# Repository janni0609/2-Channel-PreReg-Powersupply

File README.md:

# 2-Channel Pre-Regulated Bench Power Supply

A two-channel laboratory bench power supply, **0–36 V / 0–2 A per channel**, fully
isolated between channels. Each channel pairs a **tracking switch-mode
pre-regulator** with a **linear post-regulator**, so it has the low output noise of
a linear supply without the heat of dropping 36 V across a pass transistor.

Everything here is open: KiCad 10 schematics and layout for both boards, the
firmware for all three microcontrollers, and the design calculations (loop
stability, DC/DC dimensioning, ADC/DAC error budget) that back the component
values.

**Status: built and working.** Both PCBs are assembled and running. One known
footprint error, see [Known issues](#known-issues).

**Schematics in your browser (KiCanvas):**
[Main board](https://kicanvas.org/?repo=https%3A%2F%2Fgithub.com%2Fjanni0609%2F2-Channel-PreReg-Powersupply%2Ftree%2Fmain%2Fhardware_main)
· [Front panel](https://kicanvas.org/?repo=https%3A%2F%2Fgithub.com%2Fjanni0609%2F2-Channel-PreReg-Powersupply%2Ftree%2Fmain%2Fhardware_front)

---

## Specifications

| Parameter | Value |
| --- | --- |
| Channels | 2, independent, galvanically isolated from each other and from the control logic |
| Output voltage | 0 … 36 V per channel |
| Output current | 0 … 2 A per channel (setpoint = current limit, CV/CC) |
| Setpoint resolution | 12-bit DAC ≈ 8.6 mV / 0.49 mA; front panel edits in 10 mV / 1 mA steps |
| Measurement resolution | 16-bit ADC, ~1.9 mV / ~0.1 mA; displayed as 3 decimals (V) and 4 decimals (A) |
| Accuracy | ±3–4 % uncalibrated (DAC band gap dominates). **Measured after calibration, worst of both channels: setpoint ±17 mV / ±1.3 mA, readback ±2.8 mV / ±3.7 mA** — see [Measured accuracy](#measured-accuracy) |
| Protection | Per-channel over-temperature (settable, default 60 °C), system OTP on the heatsink, comms-loss shutdown, input fuses + TVS |
| Regulation | Analog CV and CC loops per channel; MCU sets the references, does not close the loop. CC is indicated by a panel LED driven straight from the loop |
| Display | 256×64 SSD1322 OLED |
| Remote control | SCPI over Ethernet (raw TCP, port 5025) and USB CDC (front-panel USB-C) |
| Cooling | Temperature-controlled 4-wire PWM fan |
| Input | 2 × 40 V DC (channels) + 12 V DC (logic) — see [Power input](#power-input) |

---

## How it works

### Power path (one channel)

```text
40 V in ──▶ LT8612 tracking buck ──▶ Vpre = Vout + 2.2 V ──▶ TIP125 linear pass ──▶ OUT
                    ▲                                              ▲
                    └────────── follows the output ────────────────┘
```

The buck converter does not produce a fixed rail — it **tracks the output**,
holding just 2.2 V of headroom across the linear stage. At full load that is
~200 mV across the 0.1 Ω shunt plus ~2 V across the TIP125 Darlington, i.e. a few
watts of dissipation instead of the ~70 W a plain 40 V linear supply would burn at
0 V out into 2 A.

The linear stage is a classic op-amp regulator built around a **TIP125** PNP
Darlington driven by a **TLV4387** quad op-amp:

- **Voltage loop** — a 4-resistor difference amplifier across OUT+/OUT− scales the
  output by 1/15 (0.06935) and compares it against `Vset` from the DAC.
- **Current loop** — a 0.1 Ω shunt (PCS2512, 1 %, 0.4 W at 2 A) is amplified ×12.25
  and compared against `Iset`. Whichever loop demands less current wins, giving
  automatic CV → CC crossover. The crossover point itself is picked off as a
  `CC/CV` signal that lights the front-panel **CC** lamp directly — no firmware in
  the path, so the indicator is as fast as the loop it reports on.

Both loops are compensated deliberately, not guessed — see
[`Calc/Stability/`](Calc/Stability/) for the plant models, the chosen compensator
values, and the loop-gain / step-response plots.

Per-channel auxiliary rails come off the 40 V input: **LMR51606** buck → 4.5 V,
**AP7384-33Y** → 3.3 V for the MCU and converters, and an **LM2776** charge pump +
**XC6901** negative LDO → −1.2 V so the op-amps can swing cleanly down to 0 V.

### Control architecture

```text
        ┌──────────────── Front panel ────────────────┐
        │  SSD1322 OLED · encoder · 6 buttons · LEDs  │
        └──────────────────────┬──────────────────────┘
                               │ SPI / I²C
                    ┌──────────┴──────────┐        ┌──────────────┐
   Ethernet ────────┤   RP2350 "Brain"    ├────────┤ W5500 · USB  │ SCPI
                    └─────┬─────────┬─────┘        └──────────────┘
                UART0 ◄───┘         └───► UART1     (1 Mbps, ISO6721 isolated)
                  │                         │
        ┌─────────┴────────┐      ┌─────────┴────────┐
        │ ATtiny1614  CH1  │      │ ATtiny1614  CH2  │
        │ ADS1118 · MCP48F │      │ ADS1118 · MCP48F │
        └──────────────────┘      └──────────────────┘
```

Each channel has its own **ATtiny1614** living in that channel's isolated ground
domain. It drives the **MCP48FVB22** dual DAC (the V and I references for the
analog loops), reads the **ADS1118** 16-bit ADC (output voltage and shunt current),
monitors an NTC, sequences the two enable lines, and stores its calibration in
EEPROM. Over-temperature shutdown happens in the channel MCU itself, so a hung
UART link can never leave an output enabled.

The **RP2350** brain owns the user interface and all remote control. It never
touches the analog loops directly; it only sends setpoints and reads telemetry
over the two isolated 1 Mbps UART links.

---

## Boards

### `hardware_main/` — main board (`DualPreRegPowerSupply.kicad_pro`)

Both power channels, both channel MCUs, the brain, and the digital supply on one
PCB. Hierarchical sheets:

| Sheet | Contents |
| --- | --- |
| `Ch1Power` (×2 instances) | One complete channel — the sheet below is instantiated twice |
| ├ `Input` | 40 V input, fuse, TVS, common-mode choke |
| ├ `Power` | Channel aux rails: 4.5 V, 3.3 V, −1.2 V |
| ├ `DCDCTracking` | LT8612 tracking pre-regulator |
| ├ `Linear_PostReg` | TIP125 pass element, V and I loops, shunt, sense amps |
| ├ `DAC_ADC` | MCP48FVB22 DAC, ADS1118 ADC, filtering |
| └ `MCU` | ATtiny1614, NTC, ISO6721 isolated UART, UPDI header |
| `Control` | RP2350-Tiny, W5500 Ethernet, front-panel connectors, fan |
| └ `Digi_Power` | 12 V input → AP63200WU → 3.3 V logic rail |

Fabrication outputs (Gerbers, BOM, CPL) are in
[`hardware_main/production/`](hardware_main/production/); an interactive BOM is at
[`hardware_main/bom/ibom.html`](hardware_main/bom/ibom.html).

### `hardware_front/` — front panel (`Front Panel.kicad_pro`)

The user interface board: SSD1322 OLED header, rotary encoder with push button,
6 push buttons, 6 status LEDs (per channel: two green output-ON indicators, one
over each banana-jack pair, plus the red CC lamp), buzzer, and an **MCP23008** I²C
expander that collects the buttons and drives the buzzer. The green indicators run
off the corresponding channel's isolated 3.3 V rail, so each half of the panel
stays in its own ground domain. Fabrication outputs in
[`hardware_front/production/`](hardware_front/production/).

---

## Firmware

Both projects build with **PlatformIO**.

### `firmware/brain/main/` — RP2350 brain

Waveshare RP2350-Tiny (built against `waveshare_rp2350_zero`). Handles the OLED
UI, encoder and buttons, fan control, the UART links to both channels, and the
SCPI server on Ethernet + USB.

```sh
cd firmware/brain/main
pio run                 # build
pio run -t upload       # flash (UPF2 / USB bootloader)
```

RP2350 pin map (also documented at the top of `platformio.ini`):

| Function | Pins |
| --- | --- |
| OLED SSD1322 (SPI1) | RES 9, SCK 10, MOSI 11, DC 12, CS 13 |
| Rotary encoder (PIO quadrature) | A 14, B 15 |
| W5500 Ethernet (SPI0) | CS 17, SCK 18, MOSI 19, MISO 20, RST 21, INT 22 |
| MCP23008 expander (I²C1) | SDA 6, SCL 7, INT 8 |
| Channel UARTs @ 1 Mbps | CH1: TX 0 / RX 1 · CH2: TX 4 / RX 5 |
| Heatsink NTC / fan PWM | ADC3 (GPIO29) / GPIO26 (25 kHz) |

[`firmware/brain/UI-test/`](firmware/brain/UI-test/) is the earlier UI-only
prototype the production firmware grew out of; it is kept for display work without
the power hardware attached.

### `firmware/channel/` — ATtiny1614 channel

megaTinyCore, 16 MHz internal oscillator, flashed over UPDI. Layered cooperative
super-loop with an explicit state machine
(`INIT → SELFTEST → IDLE ↔ RUN → FAULT`). See
[`firmware/channel/README.md`](firmware/channel/README.md) for the module tree,
the state machine, and the calibration procedure.

```sh
cd firmware/channel
pio run -t fuses        # once: set OSCCFG to 16 MHz (required!)
pio run -t upload       # flash over UPDI
```

> The `-t fuses` step is not optional on a fresh part. The default fuse selects the
> 20 MHz oscillator base; with a 16 MHz build every timing (UART baud, delays,
> telemetry period) comes out 25 % off.

### Brain ↔ channel protocol

A small binary framing: `[SOF 0xA5][LEN][CMD][payload][CRC8]`, defined in
`firmware/channel/include/protocol.h` (mirrored into the brain project). The
channel pushes a telemetry frame every 100 ms (V, I, P, temperature, state,
flags) and ACK/NACKs every command. If the brain goes quiet for 1 s while an
output is on, the channel turns that output off by itself.

---

## Remote control (SCPI)

The instrument speaks an **SCPI-1999 / IEEE-488.2 subset** on two transports at
once — raw TCP port 5025 over Ethernet, and USB CDC — so it works with PyVISA,
NI-MAX, `lxi`, or a plain terminal.

```text
*IDN?                 → PreReg,PSU-2CH-36V2A,SN00001,0.2.0
APPL CH1,12.0,1.0
OUTP ON,(@1)
MEAS:VOLT? (@1)       → 12.001
MEAS:CURR? (@1)       → 0.2531
```

Channel lists (`(@1)`, `(@1,2)`) and stateful `INST:NSEL` selection are both
supported, along with the STATus register model, an error queue, and the
CALibration subsystem. The full command reference — including UART mappings and
known deviations — is in [`firmware/SCPI/commands.md`](firmware/SCPI/commands.md).

Network settings (DHCP or static IP, netmask, gateway, hostname) are configured
from the front panel under *Settings → Network*, and only take effect on **Apply**,
so a half-typed IP never goes live.

---

## Front panel

The main screen shows both channels side by side: measured voltage and current in
large digits, output power in the corner, and the active setpoints on the bottom
row. Six buttons (`V · on · I` per channel) select what the encoder edits and
toggle each output; the encoder push button moves the digit cursor — underlined on
screen — so any digit can be dialled directly instead of scrolling through the
whole range.

Below the buttons, each channel has two green output-ON LEDs flanking a red **CC**
lamp that lights whenever that channel leaves constant-voltage regulation, then the
output banana jacks. The USB-C port for SCPI-over-USB and firmware updates sits in
the middle of the panel; the mains switch is on the right. The enclosure is 3D
printed.

The Settings menu (encoder-driven, see
[`firmware/brain/UI-test/Settings.md`](firmware/brain/UI-test/Settings.md))
covers per-channel diagnostics (temperature, DAC/ADC/comms health, operating
hours, stored calibration values, the manual 2-point calibration wizard), the
temperature and fan curve (start temp, max temp, minimum speed, system OTP),
the network configuration, and system items (firmware version, beeper, brain
runtime, remember-setpoints-on-restart).

---

## Calibration

Every signal path — `VSET`, `ISET`, `VMEAS`, `IMEAS`, per channel — is a straight
line `y = gain·x + offset` fitted from two points and stored in the channel's
EEPROM. This is **required**, not optional: the MCP48FVB22 uses its internal
1.22 V band gap (Vref is not routed on the PCB), and that band gap is specified to
±3.3 %. Calibration removes it, along with the 1 % resistor and shunt tolerances,
leaving roughly ±0.05 % on voltage and ±0.1–0.2 % on current. Until a channel has
been calibrated it reports `FLAG_CAL_INVALID`.

Run it from the front panel (*Settings → Channel n → Manual Cal V/I*, with a
DMM on the output) or remotely via `CAL:POIN` / `CAL:COMM`. Full error budget and
where each term comes from:
[`Calc/DAC_ADC/DAC_ADC_Accuracy_Analysis.md`](Calc/DAC_ADC/DAC_ADC_Accuracy_Analysis.md).

---

## Measured accuracy

Both channels were measured against a **Siglent SDM3065X** 6½-digit DMM on
2026-08-03/04, using [`Calc/evaluation/psu_accuracy.py`](Calc/evaluation/) — a
ramp of the full range in fine steps, comparing three numbers at every step:

| | source | exercises |
| --- | --- | --- |
| setpoint | what was written with `VOLT` / `CURR` | DAC → `VSET`/`ISET` chain |
| readback | `MEAS:VOLT?` / `MEAS:CURR?` | sense amp → ADC → `VMEAS`/`IMEAS` chain |
| truth | SDM3065X | — |

Voltage: 0 → 36 V in 500 mV steps, open circuit. Current: 0 → 2 A in 25 mA steps
into the DMM's own current input as the load, 2 V compliance. Figures are for the
instrument **as it stands today**, i.e. calibrated, and exclude the two endpoints
the channel physically cannot reach: the 0 V / 0 A setpoint (output floor, not an
accuracy error) and the clipped top of the current range (see
[Known issues](#known-issues)). `psu_accuracy.py` applies both exclusions itself,
so these numbers come straight out of its report; `--keep-endpoints` reports every
point instead.

### Results

| | CH1 setpoint | CH1 readback | CH2 setpoint | CH2 readback |
| --- | --- | --- | --- | --- |
| **Voltage** rms | 8.8 mV | **0.74 mV** | 5.1 mV | 1.4 mV |
| worst | 16.5 mV | 2.1 mV | 11.6 mV | 2.8 mV |
| gain error | −0.0005 % | +0.0025 % | −0.0024 % | −0.0003 % |
| **Current** rms | **0.30 mA** | 0.12 mA | **0.52 mA** | 0.16 mA |
| worst | 0.79 mA | 0.39 mA | 1.36 mA | 0.51 mA |
| gain error | +0.012 % | +0.013 % | +0.035 % | +0.019 % |

Both current columns were re-measured on 2026-08-04, after the measure-path
calibration bug was found and fixed and both channels' `IMEAS` re-calibrated.
The readback paths went from 0.78 mA rms / +0.135 % gain / −1.38 mA offset (CH1)
and 2.0 mA rms / +0.176 % gain (CH2) to the numbers above — an order of
magnitude, and the −1.4 mA offset that had been blamed on the shunt turned out to
be an artefact of the bad fit.

In short, worst of both channels: **voltage setpoint ±17 mV (≈0.05 % FS), voltage
readback ±2.8 mV, current setpoint ±1.4 mA (≈0.07 % FS), current readback
±0.51 mA**. Every voltage gain error is inside ±0.003 % and every current gain
error is now inside ±0.04 %, so the calibration is doing its job on every path.
The current readback is at ~5 ADC LSB worst case.

<picture>
  <source media="(prefers-color-scheme: dark)" srcset="Calc/evaluation/results/ramp_v_ch1_20260804_231349_ch1_v_baseline_dark.png">
  
</picture>

The voltage setpoint trace is the interesting one. Its error is **not**
calibration error — it is the 12-bit DAC. The sawtooth is the ±½ LSB rounding of
a requested millivolt onto the ~8.9 mV code grid, and the slow envelope on top is
the DAC's own INL (specified ±2 LSB). A 2-point calibration pins the two
endpoints and cannot bend to follow a bow between them, which is why
re-calibrating an already-calibrated channel here changes nothing. The readback
trace sits flat at the ADC's ~1.8 mV quantum. **This is the hardware floor, not a
tuning problem** — improving it needs an external DAC reference (the `Vref` pin is
not routed) or more DAC bits.

<picture>
  <source media="(prefers-color-scheme: dark)" srcset="Calc/evaluation/results/ramp_i_ch1_20260804_224335_ch1_imeas_fix_dark.png">
  
</picture>

Current is the opposite case, and shows what calibration *can* do. Both of CH1's
current paths were a clean tilt beforehand — an error proportional to reading,
which is exactly the shape a 2-point fit removes. The setpoint went from +0.176 %
gain (−1.2 mA at 100 mA rising to +1.8 mA at 2 A) to +0.012 %, rms 0.89 →
0.30 mA; the readback went from +0.135 % gain with a −1.38 mA offset to
+0.013 %, rms 0.78 → 0.12 mA. Both traces are now flat inside ±0.8 mA across the
range, with the readback at ~4 ADC LSB. CH2 behaves the same way.

**Rule of thumb from this:** plot the error against reading before calibrating. A
*tilt*, or a constant offset, is gain/offset error and a 2-point fit removes it
exactly. A *bow* between the cal points is INL and it will not — which is why the
voltage setpoint above does not improve however often it is re-run. The report's
`worst non-linearity` row measures that bow; compare it against the quantisation
floor printed beneath it.

All raw data, per-run reports and both channels' plots are in
[`Calc/evaluation/results/`](Calc/evaluation/results/); the harness, wiring and
options are documented in [`Calc/evaluation/README.md`](Calc/evaluation/README.md).

---

## Power input

The supply is fed from three off-the-shelf Mean Well modules:

| Input | Supply | Feeds |
| --- | --- | --- |
| J101 | Mean Well **LRS-75-36**, trimmed to **40 V** | Channel 1 |
| J601 | Mean Well **LRS-75-36**, trimmed to **40 V** | Channel 2 |
| J901 | Mean Well **RS-15-12** (12 V) | Brain, OLED, Ethernet, fan |

Each channel input has its own 3.5 A fuse, TVS clamp, and common-mode choke.
Because the two channel supplies are separate isolated modules and the UART links
are isolated with ISO6721 digital isolators, the two outputs are genuinely
floating and independent — they can be wired in series or referenced separately.

Outputs terminate in front-panel banana jacks (J201/J202 and J402/J403).

---

## Repository layout

```text
hardware_main/     KiCad 10 project — main board (power, MCUs, brain)
hardware_front/    KiCad 10 project — front panel (OLED, encoder, buttons)
firmware/
  brain/main/      RP2350 production firmware (UI + comms + SCPI)
  brain/UI-test/   Earlier UI-only prototype
  channel/         ATtiny1614 channel firmware
  SCPI/            SCPI command reference
  requirements/    Original firmware requirements notes
  Datasheets/      Datasheets for the main ICs
Calc/
  Stability/       V and I loop compensation — notebooks + typeset report
  DCDC Calc/       LMR51606 40 V → 4.5 V aux buck design
  DAC_ADC/         Setpoint/measurement error budget
  evaluation/      Bench accuracy measurement vs a reference DMM (+ raw results)
```

---

## Design notes and calculations

- [`Calc/Stability/stepbystep/`](Calc/Stability/stepbystep/) — Jupyter notebooks
  deriving the voltage and current loop transfer functions (including the TIP125's
  β(s) roll-off and the op-amp GBW corner), the chosen compensator values, load
  sweeps, and step responses. The typeset summary is
  `Calc/Stability/stepbystep/report/loop_analysis.pdf`.
- [`Calc/DCDC Calc/LMR51606X_40V_4V5_200mA_design.md`](Calc/DCDC%20Calc/LMR51606X_40V_4V5_200mA_design.md)
  — full worked design of the 40 V → 4.5 V auxiliary buck.
- [`Calc/DAC_ADC/DAC_ADC_Accuracy_Analysis.md`](Calc/DAC_ADC/DAC_ADC_Accuracy_Analysis.md)
  — where every microvolt of error comes from, and what calibration does and does
  not fix.

---

## Known issues

- **AP7384-33Y footprint (channel 3.3 V LDO)** — the footprint on the main board is
  wrong; the part needs rework/adaptation to fit. Fix before ordering new boards.
- The ADS1118 PGA is **pinned to ±4.096 V** rather than autoscaling. Each PGA range
  has its own gain/offset error and input impedance, so a single 2-point cal line
  cannot describe all of them — autoscaling made readings drift away from the
  calibration points. Re-enabling it requires per-range calibration
  (`ADC_PGA_*_INDEX` in `firmware/channel/include/config.h`).
- **Neither channel reaches its rated 2.000 A.** The ISET DAC clips at ~1.99 A on
  CH1 and ~1.95 A on CH2 (both setpoints above the ceiling return the identical
  current, and the readback agrees). Full scale is 2.44 V ÷ 1.225 V/A = 1.99 A,
  but `DEFAULT_I_DIV` in `calibration.cpp` assumes 1.2 → 2.033 A and
  `SETPOINT_I_MAX_MA` is 2000; the channel spread on top is band-gap and shunt
  tolerance. The top ~1–2 % of the current range is not reachable.
- `CALibration:DATA?` returns NaN over SCPI: gain/offset cannot currently be read
  back across the channel link. `CAL:POINt`/`CAL:COMMit` are also fire-and-forget
  — the channel's NACK lands in `lastNackCmd` and the SCPI handler never looks at
  it — so a rejected commit is invisible to the host. Between them these kept a
  (now fixed) measure-path calibration bug hidden for far longer than it should
  have been. Until they are addressed, re-drive the cal points and check the
  readback residual (as `psu_accuracy.py` now does) rather than trusting
  `CAL:VALid?`.
- **A setpoint written immediately after `CAL:COMMit` is occasionally dropped.**
  Seen 3/3 times as the first `CURR` after committing `IMEAS` in a full
  calibration sequence, and 0/17 in isolated retries — so it is real but not yet
  root-caused. Ruled out: the channel is not stalled by the EEPROM write (the
  link never drops, `OUTP?` held over 3592 samples across a commit), and it is
  not a frame-size overflow. Leave a settle after a commit, and verify setpoints
  actually landed before measuring against them.
- The hostname set in *Settings → Network* is stored and displayed, but the stock
  Ethernet DHCP client does not advertise it to the DHCP server.
- The CV/CC mode is shown on the panel by a hardware-driven LED, but the `CC/CV`
  signal is not routed to a channel MCU pin, so the regulation mode cannot be
  queried over SCPI (`STAT:OPER` has no constant-current bit).

---

## Tools

KiCad 10 · PlatformIO (`raspberrypi` + `atmelmegaavr` platforms) · megaTinyCore ·
Arduino-Pico core · Python/Jupyter for the analysis notebooks.

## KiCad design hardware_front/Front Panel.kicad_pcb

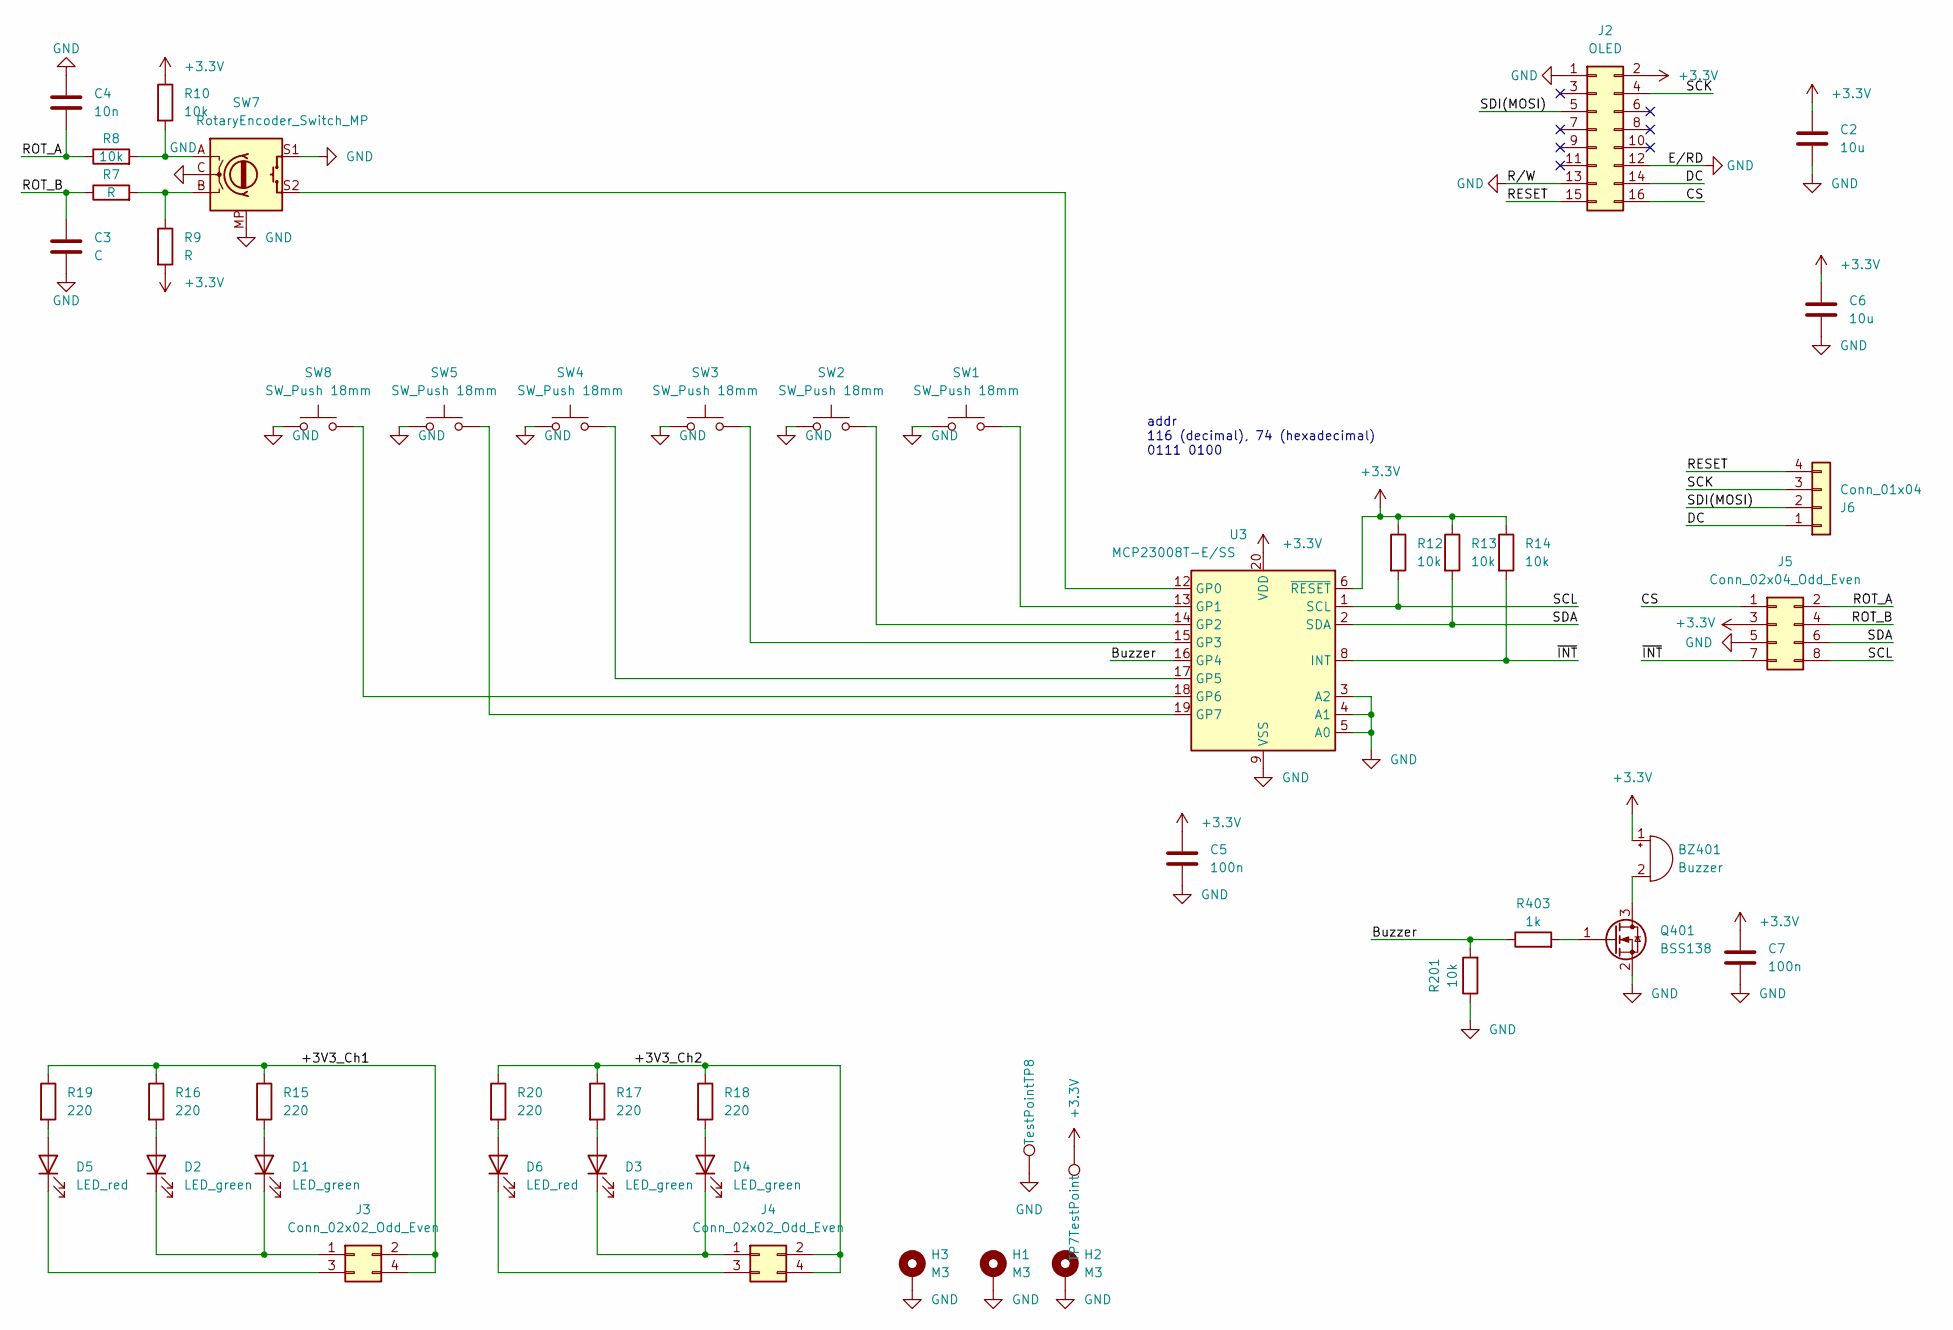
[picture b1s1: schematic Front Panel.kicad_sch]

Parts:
BZ401: Buzzer; Buzzer_12x9.5RM7.6
C2, C6: 10u; C_0805_2012Metric
C3: C; C_0603_1608Metric
C4: 10n; C_0603_1608Metric
C5, C7: 100n; C_0603_1608Metric
D1, D2, D3, D4: LED_green; LED_D3.0mm_FlatTop
D5, D6: LED_red; LED_D3.0mm_FlatTop
H1, H2, H3: M3; MountingHole_3.2mm_M3_DIN965_Pad
J2: OLED; PinSocket_2x08_P2.54mm_Vertical
J3, J4: Conn_02x02_Odd_Even; PinSocket_2x02_P2.54mm_Vertical
J5: Conn_02x04_Odd_Even; PinSocket_2x04_P2.54mm_Vertical
J6: Conn_01x04; PinSocket_1x04_P2.54mm_Vertical
Q401: BSS138; SOT-23-3
R7, R9: R; R_0603_1608Metric
R8, R10, R12, R13, R14, R201: 10k; R_0603_1608Metric
R15, R16, R17, R18, R19, R20: 220; R_0603_1608Metric
R403: 1k; R_0603_1608Metric
SW1, SW2, SW3, SW4, SW5, SW8: SW_Push 18mm; SW_PUSH_6mm_H13mm
SW7: RotaryEncoder_Switch_MP; RotaryEncoder_Alps_EC11E-Switch_Vertical_H20mm
TP7, TP8: TestPoint; TestPoint_Pad_D1.5mm
U3: MCP23008T-E/SS; SSOP-20_5.3x7.2mm_P0.65mm

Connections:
+3.3V: BZ401.1 (+), C2.1, C5.1, C6.1, C7.1, J2.2, J5.3, R9.2, R10.1, R12.1, R13.1, R14.1, TP7.1 (1_1), U3.6 (~RESET), U3.20 (VDD)
/+3V3_Ch1: J3.2, J3.4, R15.1, R16.1, R19.1
/+3V3_Ch2: J4.2, J4.4, R17.1, R18.1, R20.1
/Buzzer: R201.2, R403.1, U3.16 (GP4)
/CS: J2.16, J5.1
/DC: J2.14, J6.1
/RESET: J2.15, J6.4
/ROT_A: C4.1, J5.2, R8.1
/ROT_B: C3.1, J5.4, R7.1
/SCK: J2.4, J6.3
/SCL: J5.8, R12.2, U3.1 (SCL)
/SDA: J5.6, R13.2, U3.2 (SDA)
/SDI(MOSI): J2.5, J6.2
/~INT: J5.7, R14.2, U3.8 (INT)
GND: C2.2, C3.2, C4.2, C5.2, C6.2, C7.2, H1.1 (1_1), H2.1 (1_1), H3.1 (1_1), J2.1, J2.12, J2.13, J5.5, Q401.2 (S), R201.1, SW1.1, SW2.1, SW3.1, SW4.1, SW5.1, SW7.C, SW7.MP, SW7.S1, SW8.1, TP8.1 (1_1), U3.3 (A2), U3.4 (A1), U3.5 (A0), U3.9 (VSS)
unnamed: BZ401.2 (-), Q401.3 (D)
unnamed: D1.2 (A), R15.2
unnamed: D1.1 (K), D2.1 (K), J3.1
unnamed: D2.2 (A), R16.2
unnamed: D3.2 (A), R17.2
unnamed: D3.1 (K), D4.1 (K), J4.1
unnamed: D4.2 (A), R18.2
unnamed: D5.2 (A), R19.2
unnamed: D5.1 (K), J3.3
unnamed: D6.2 (A), R20.2
unnamed: D6.1 (K), J4.3
unnamed: Q401.1 (G), R403.2
unnamed: R7.2, R9.1, SW7.B
unnamed: R8.2, R10.2, SW7.A
unnamed: SW7.S2, U3.12 (GP0)
unnamed: SW1.2, U3.13 (GP1)
unnamed: SW2.2, U3.14 (GP2)
unnamed: SW3.2, U3.15 (GP3)
unnamed: SW4.2, U3.17 (GP5)
unnamed: SW8.2, U3.18 (GP6)
unnamed: SW5.2, U3.19 (GP7)

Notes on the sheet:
addr 116 (decimal), 74 (hexadecimal) 0111 0100

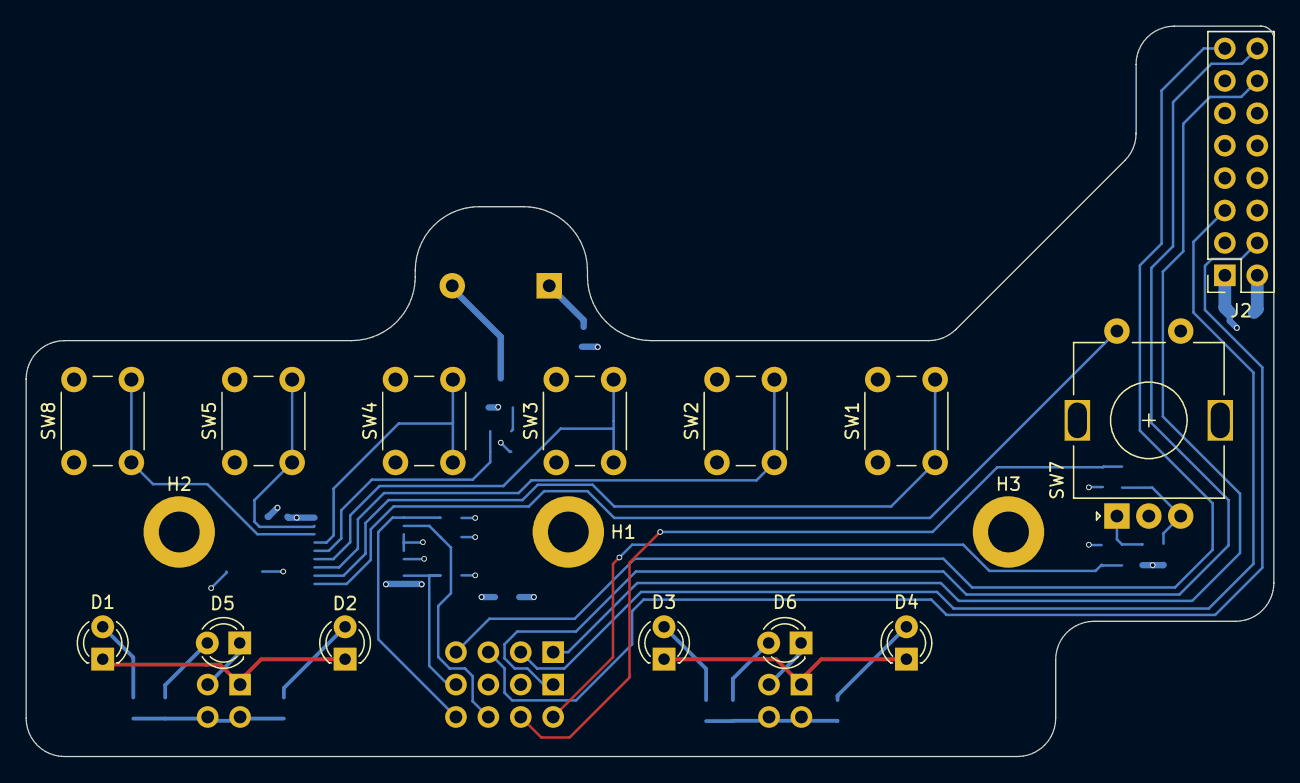
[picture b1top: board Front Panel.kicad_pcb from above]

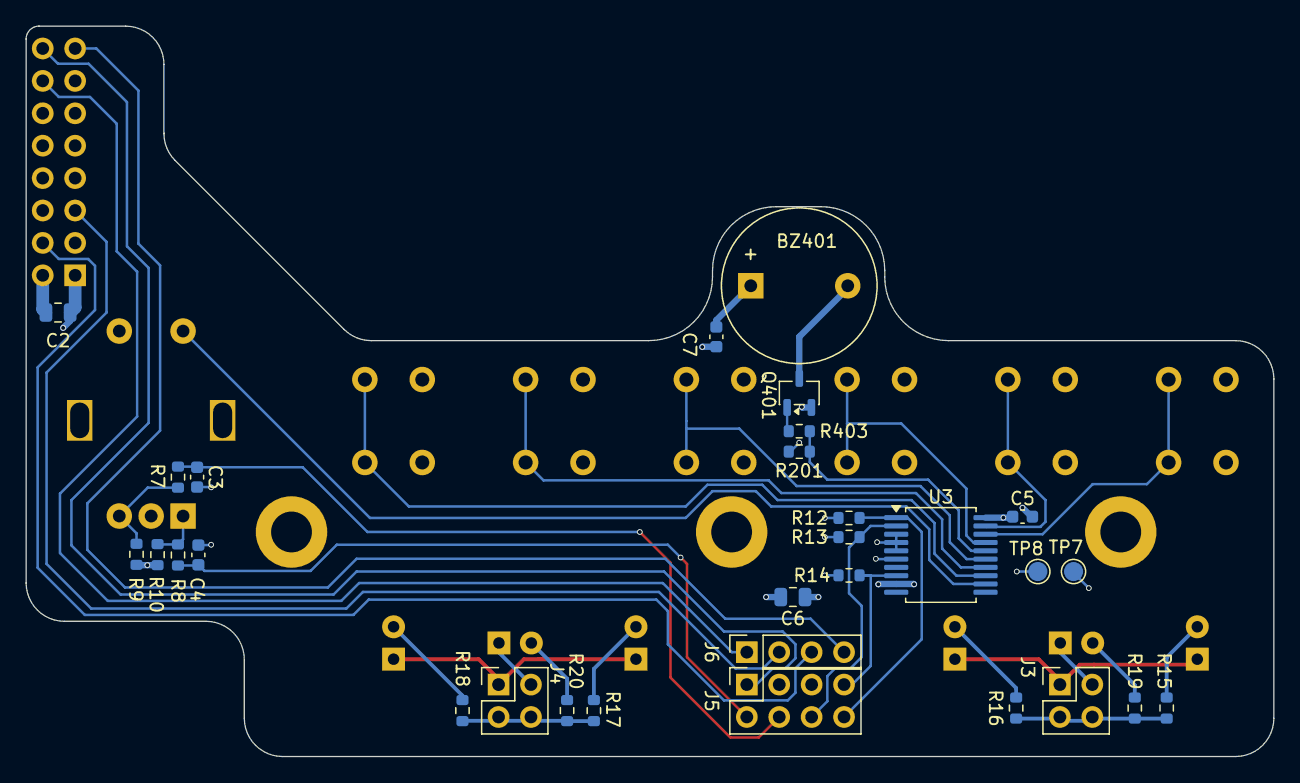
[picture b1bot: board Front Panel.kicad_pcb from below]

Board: 4 copper layers, 97.8 x 57.2 mm, 47 parts (30 on the bottom side), 36 nets.

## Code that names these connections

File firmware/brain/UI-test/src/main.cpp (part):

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#include <string.h>

// ── Front-panel OLED wiring (SSD1322 256x64) on the RP2350-Tiny brain ──────────
//   RES  -> GPIO9     reset          (manual GPIO)
//   SCK  -> GPIO10    SPI1 SCK
//   MOSI -> GPIO11    SPI1 TX
//   DC   -> GPIO12    data/command   (manual GPIO)
//   CS   -> GPIO13    chip select    (manual GPIO)
// GPIO10/GPIO11 are the SPI1 clock/data functions, so the driver uses SPI1.
#define PIN_RES  9
#define PIN_SCK  10
#define PIN_MOSI 11
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#define PIN_CS   13

// ── Rotary encoder quadrature (direct wiring). The ROT signals are active-low,
// so the inputs use pull-ups; a closed contact pulls the pin down. GPIO17 is just
// held high for the current hookup. The encoder PUSH button no longer lives here —
// it moved to the MCP23008 I/O expander (GP0), read over I2C below.
//   ROT_A  -> GPIO14   quadrature A   (PIO in-base; A/B must be consecutive)
//   ROT_B  -> GPIO15   quadrature B
//   GPIO17 -> driven high
#define PIN_ENC_A   14
#define PIN_ENC_B   15
#define PIN_ENC_PWR 17

// ── Front-panel buttons + buzzer on an MCP23008 I/O expander (I2C1) ────────────
// The RP2350 exposes I2C1 SDA/SCL on GPIO6/GPIO7 (I2C0 cannot reach those pins),
// so the expander lives on the Wire1 peripheral. Its INT pin flags any button
// change on GPIO8; we read GPIO to identify the change and clear the interrupt.
//   SDA -> GPIO6   (I2C1 SDA)
//   SCL -> GPIO7   (I2C1 SCL)
//   INT -> GPIO8   (active-low, open-drain w/ external pull-up; low on change)
#define PIN_MCP_SDA 6
#define PIN_MCP_SCL 7
#define PIN_MCP_INT 8
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#define MCP_CH2_I  (1 << 1)   // GP1  select CH2 current setpoint for editing
#define MCP_CH2_ON (1 << 2)   // GP2  CH2 output toggle (placeholder)
#define MCP_CH2_V  (1 << 3)   // GP3  select CH2 voltage setpoint for editing
#define MCP_BUZZER (1 << 4)   // GP4  buzzer (active-high output)
#define MCP_CH1_I  (1 << 5)   // GP5  select CH1 current setpoint for editing
#define MCP_CH1_V  (1 << 6)   // GP6  select CH1 voltage setpoint for editing
#define MCP_CH1_ON (1 << 7)   // GP7  CH1 output toggle (placeholder)

// All pins except the buzzer (GP4) are button inputs.
static const uint8_t MCP_BTN_MASK = (uint8_t)~MCP_BUZZER;   // 0xEF

SSD1322 display(SPI1, PIN_CS, PIN_DC, PIN_RES, PIN_SCK, PIN_MOSI);
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    return Wire1.available() ? (uint8_t)Wire1.read() : 0xFF;
}

// Drive the buzzer (GP4). Kept as a shadow write so the input pins are untouched.
static void mcpSetBuzzer(bool on) {
    if (on) mcpOlat |= MCP_BUZZER;
    else    mcpOlat &= (uint8_t)~MCP_BUZZER;
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
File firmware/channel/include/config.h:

/**
 * config.h - Board pin map, build-time constants and tunables for the
 *            power-supply CHANNEL firmware (ATtiny1614 @ 3.3 V).
 *
 * All hardware-specific numbers live here so the rest of the code stays
 * portable and readable. Pins use megaTinyCore's PIN_Pxn macros.
 *
 * NOTE ON ADC_CS: the requirements doc lists ADC_CS on PA3, which collides
 * with SCK. The bus is shared (MOSI/MISO/SCK on PA1/PA2/PA3) so ADC_CS must
 * be its own line; it is wired to PA4 (the ATtiny1614 default SPI SS).
 */
#ifndef CHANNEL_CONFIG_H
#define CHANNEL_CONFIG_H

#include <Arduino.h>

/* ------------------------------------------------------------------ */
/* Pin map (ATtiny1614, 14-pin SOIC)                                  */
/* ------------------------------------------------------------------ */

/* Shared SPI bus (handled by the SPI library on the default pins):
 *   MOSI = PA1, MISO = PA2, SCK = PA3                                 */
#define PIN_ADC_CS      PIN_PA4   /* ADS1118    chip select (active low) */
#define PIN_DAC_CS      PIN_PA7   /* MCP48FVB22 chip select (active low) */
#define PIN_DAC_LAT     PIN_PA6   /* MCP48FVB22 latch (active low)       */

/* Output enable lines */
#define PIN_EN_DCDC     PIN_PB1   /* Enable_DCDC : pre-regulator (buck)  */
#define PIN_EN_LIN      PIN_PA5   /* Enable_lin  : linear post-regulator */

/* Thermistor divider (on-chip ADC input) */
#define PIN_NTC         PIN_PB0   /* 10k NTC, Rtop=10k to VDD, Rbot=NTC  */

/* UART to the Brain is USART0 on PB2(TX)/PB3(RX) -> the 'Serial' object */
#define BRAIN_UART      Serial
#define BRAIN_BAUD      1000000UL   /* 1 Mbps; exact at F_CPU=16 MHz (BAUD reg = 64) */

/* ------------------------------------------------------------------ */
/* NTC thermistor (10k, B=3380K, beta model)                          */
/* ------------------------------------------------------------------ */
#define NTC_R_TOP_OHMS      10000.0f   /* fixed top resistor to VDD       */
#define NTC_R0_OHMS         10000.0f   /* NTC nominal resistance @ T0     */
#define NTC_T0_KELVIN       298.15f    /* 25 C                            */
#define NTC_BETA            3380.0f    /* B-constant (K)                  */
#define NTC_ADC_BITS        10         /* analogRead resolution we use    */

/* ------------------------------------------------------------------ */
/* Thermal protection                                                 */
/* ------------------------------------------------------------------ */
/* The trip point is runtime-settable per channel (CMD_SET_OTP, persisted in
 * the settings EEPROM, clamped to OTP_MIN_C..OTP_MAX_C). This is only the value
 * used to seed a blank EEPROM. Recovery is TEMP_OTP_HYST_C below the trip. */
#define TEMP_OTP_DEFAULT_C  60u        /* shut output off at/above this   */
#define TEMP_OTP_HYST_C     5.0f       /* re-arm this far below the trip  */

/* ------------------------------------------------------------------ */
/* Comms-loss watchdog                                                */
/* ------------------------------------------------------------------ */
/* While the output is on, the Brain must be heard from within this
 * window or the channel trips the output off (safe state). The Brain
 * pings every LINK_HEARTBEAT_MS (250) so a healthy link never trips;
 * this leaves ~4 missed heartbeats of margin against loop jitter.    */
#define COMMS_TIMEOUT_MS    1000u
#define TEMP_SELFTEST_MIN_C (-10.0f)   /* startup must be within this ... */
#define TEMP_SELFTEST_MAX_C 60.0f      /* ... range                       */

/* ------------------------------------------------------------------ */
/* DAC (MCP48FVB22) - internal band gap, gain 1x -> 0..2.44 V FS       */
/* ------------------------------------------------------------------ */
#define DAC_FULLSCALE_V     2.44f      /* VRL = 2 x 1.22V band gap, G=1x  */
#define DAC_MAX_CODE        4095u      /* 12-bit                          */

/* ------------------------------------------------------------------ */
/* ADC (ADS1118)                                                      */
/* ------------------------------------------------------------------ */
/* Front-end full scale sits near +-4.096 V. Indices map to ADS1118 PGA.
 *
 * The PGA is PINNED to +-4.096 V (MAX == MIN disables the autoscaler in
 * measure.cpp): each PGA range has its own gain/offset error and its own
 * input impedance loading the sense divider, so with autoscaling the measure
 * path is a different transfer function per range. A single 2-point cal line
 * cannot model that -- readings were only correct at the two cal points and
 * drifted by the inter-range mismatch everywhere else. One fixed range gives
 * one consistent line. LSB at +-4.096: ~1.9 mV / ~0.1 mA at the output,
 * matching the display resolution; averaging covers the last digit.
 * (Re-enable autoscale only together with a per-range calibration scheme.) */
#define ADC_PGA_START_INDEX     1u     /* 001 = +-4.096 V                 */
#define ADC_PGA_MIN_INDEX       1u     /* never below this (>= no benefit)*/
#define ADC_PGA_MAX_INDEX       1u     /* pinned to +-4.096 V (see above) */
#define ADC_AUTOSCALE_UP_PCT    88     /* |code| above % FS -> lower gain */
#define ADC_AUTOSCALE_DN_PCT    42     /* |code| below % FS -> higher gain*/

/* ------------------------------------------------------------------ */
/* Measurement averaging                                              */
/* ------------------------------------------------------------------ */
/* Default moving-average window length (samples) for the V and I
 * readings, used the first time the settings EEPROM is seeded. 1 = no
 * averaging. The Brain can change it per channel (1..AVG_MAX); the value
 * persists in the channel's EEPROM. */
#define MEAS_AVG_DEFAULT        1u

/* ------------------------------------------------------------------ */
/* Runtime (operating-hours) meter                                    */
/* ------------------------------------------------------------------ */
/* Accumulated powered-on seconds are flushed to EEPROM this often, not
 * continuously, to bound cell wear. Endurance is ~100k writes; at one save
 * per interval that is ~100k * interval of operation before wear-out. The
 * cost is that up to this many seconds of the current session are lost on an
 * unexpected power-off. 300 s trades ~5 min worst-case loss for ~9.5 years of
 * continuous operation (far longer intermittently). Display is in whole hours,
 * so a few dropped minutes never change what the user sees. */
#define RUNTIME_SAVE_INTERVAL_S   300u

/* ------------------------------------------------------------------ */
/* Task periods (ms) for the cooperative scheduler                    */
/* ------------------------------------------------------------------ */
#define PERIOD_THERMAL_MS       100u
#define PERIOD_TELEMETRY_MS     100u
#define PERIOD_HOUSEKEEP_MS     1000u
/* measurement paces itself off the ADC conversion time, see measure.cpp */

/* ------------------------------------------------------------------ */
/* Setpoint limits (engineering units, see README for the convention) */
/* ------------------------------------------------------------------ */
#define SETPOINT_V_MAX_MV       36000   /* clamp for incoming set voltage  */
#define SETPOINT_I_MAX_MA       2000    /* clamp for incoming set current  */

#endif /* CHANNEL_CONFIG_H */

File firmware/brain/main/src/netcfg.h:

/**
 * netcfg.h - W5500 Ethernet bring-up, persisted LAN configuration and the SCPI
 *            TCP transport (raw socket, port 5025) for the RP2350 brain.
 *
 * Wiring (RP2350, hardware SPI0 — the OLED keeps SPI1 so the two never contend):
 *   CS  -> GPIO17   SCK -> GPIO18   MOSI -> GPIO19   MISO -> GPIO20
 *   RST -> GPIO21   INT -> GPIO22 (unused; the Ethernet library polls the W5500)
 *
 * The module owns the editable/persisted LAN settings (DHCP flag, static
 * IP/netmask/gateway/DNS, hostname). The front-panel Network submenu and the
 * SCPI SYSTem:COMMunicate:LAN commands both read and mutate these through the
 * accessors below, then call netcfg_apply() to (re)configure the interface.
 *
 * The MAC address is derived once from the RP2350 unique chip id (locally
 * administered, unicast) so every unit is unique without any stored value; it is
 * read-only.
 */
#ifndef BRAIN_NETCFG_H
#define BRAIN_NETCFG_H

#include <stdint.h>

/* Max hostname length incl. NUL (DHCP option 12 / display). */
#define NETCFG_HOSTNAME_MAX 24

/* SCPI instrument port (raw TCP, the standard SCPI-RAW "instrument" socket). */
#define NETCFG_SCPI_PORT 5025

/* Bring up the W5500 and start the SCPI TCP server. Loads the persisted config
 * (defaults applied if absent/corrupt) and derives the MAC. In DHCP mode this
 * blocks on the lease request, but bounded (see NET_DHCP_INIT_TIMEOUT_MS), so a
 * missing cable/server only delays boot — it can never hang it. Call once from
 * setup() AFTER EEPROM.begin(). */
void netcfg_init();

/* Service the transport every loop: accept new SCPI clients, drain their RX into
 * the SCPI parser, prune dropped connections and renew the DHCP lease.
 * Bounded: the only blocking work is a DHCP re-acquisition, which is rate-limited
 * to NET_DHCP_RETRY_PERIOD_MS and budgeted below the channel comms watchdog. */
void netcfg_task();

/* Re-configure the interface from the current (pending) config and persist it.
 * Drops existing SCPI connections. Invoked by the menu "Apply" row and by the
 * SYST:COMM:LAN SCPI setters. */
void netcfg_apply();

/* Persist the current config to EEPROM without touching the live interface. */
void netcfg_save();

/* Request a deferred netcfg_apply(): the reconfigure runs at the top of the next
 * netcfg_task(), never mid-way through servicing a client. Used by the SCPI
 * SYST:COMM:LAN setters, which run inside client RX handling and must not tear
 * down the very socket they are being read from. */
void netcfg_request_apply();

/* --- Pending (editable, persisted) configuration ------------------------------ */
bool        netcfg_dhcp();
void        netcfg_set_dhcp(bool on);
void        netcfg_get_ip(uint8_t out[4]);     void netcfg_set_ip(const uint8_t v[4]);
void        netcfg_get_mask(uint8_t out[4]);   void netcfg_set_mask(const uint8_t v[4]);
void        netcfg_get_gw(uint8_t out[4]);     void netcfg_set_gw(const uint8_t v[4]);
void        netcfg_get_dns(uint8_t out[4]);    void netcfg_set_dns(const uint8_t v[4]);
const char *netcfg_hostname();                 void netcfg_set_hostname(const char *s);

/* --- Live interface status (what the W5500 actually has right now) ------------- */
bool netcfg_hw_present();     /* true once a W5500 responded at init          */
bool netcfg_link_up();        /* PHY link (cable) up                          */
bool netcfg_has_ip();         /* a non-zero IPv4 address is configured        */
void netcfg_live_ip(uint8_t out[4]);
void netcfg_live_mask(uint8_t out[4]);
void netcfg_live_gw(uint8_t out[4]);
void netcfg_mac(uint8_t out[6]);
int  netcfg_client_count();   /* number of connected SCPI clients             */

#endif /* BRAIN_NETCFG_H */

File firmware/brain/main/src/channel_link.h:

/**
 * channel_link.h - Brain-side UART link to the two per-channel ATtiny1614
 *                  boards, using the shared framed protocol (protocol.h).
 *
 * Wiring (RP2350, see platformio.ini / Control.kicad_sch):
 *   CH1 = UART0 (Serial1):  TX GPIO0 -> Rx_Ch1,  RX GPIO1 <- Tx_Ch1
 *   CH2 = UART1 (Serial2):  TX GPIO4 -> Rx_Ch2,  RX GPIO5 <- Tx_Ch2
 * Both run at 1 Mbps to match the channel's BRAIN_BAUD.
 *
 * The channel pushes a CMD_TELEMETRY frame every ~100 ms unsolicited, so this
 * module mostly listens: channel_link_task() drains both UARTs, decodes frames
 * and keeps a per-channel status snapshot. A link is flagged "down" when no
 * valid telemetry has arrived within LINK_TIMEOUT_MS. Commands (set voltage /
 * current / output, calibration, fault reset) are one-shot sends.
 */
#ifndef BRAIN_CHANNEL_LINK_H
#define BRAIN_CHANNEL_LINK_H

#include <stdint.h>

/* Channel indices (also the array index into the status table). */
enum { LINK_CH1 = 0, LINK_CH2 = 1, LINK_COUNT = 2 };

/* A link is considered down if no telemetry arrives within this window
 * (5 missed 100 ms telemetry pushes). */
#define LINK_TIMEOUT_MS   500u

/* How often the Brain pings each channel. This is the channel's comms-loss
 * watchdog heartbeat: the channel trips its output off if it hears nothing
 * for COMMS_TIMEOUT_MS (1000 ms), so pinging at 250 ms keeps a healthy but
 * idle link fed with ~4 missed-ping margin. Must stay well below the
 * channel's COMMS_TIMEOUT_MS. */
#define LINK_HEARTBEAT_MS 250u

/* Latest snapshot for one channel: decoded telemetry plus link health. */
struct ChannelStatus {
    /* --- decoded CMD_TELEMETRY --- */
    int32_t  v_mV;        /* measured output voltage (mV)                 */
    int32_t  i_dmA;       /* measured output current (0.1 mA units)       */
    int32_t  p_mW;        /* measured output power   (mW)                 */
    int16_t  temp_cC;     /* temperature (centi-Celsius, 2531 = 25.31 C)  */
    uint8_t  state;       /* ST_* run-state                               */
    uint8_t  flags;       /* FLAG_* status bits                           */

    /* --- per-channel settings (from CMD_SETTINGS) --- */
    uint8_t  avgV;        /* voltage measurement averaging window (1..32)  */
    uint8_t  avgI;        /* current measurement averaging window (1..32)  */
    uint8_t  otpC;        /* over-temperature trip point, deg C            */
    uint32_t runtimeS;    /* channel operating-hours meter (seconds)       */
    bool     avgValid;    /* true once CMD_SETTINGS has been received       */

    /* --- link health / bookkeeping --- */
    bool     linkUp;      /* telemetry seen within LINK_TIMEOUT_MS        */
    uint32_t lastRxMs;    /* millis() of the last valid frame             */
    uint32_t framesRx;    /* total valid frames received                 */
    uint32_t crcErrors;   /* frames dropped on a bad CRC                  */
    uint32_t rxOverflows; /* times the UART RX buffer overflowed (drops)  */

    /* --- last async notifications --- */
    uint8_t  lastEvent;       /* last EVT_* code (0 = none yet)           */
    uint8_t  lastAckCmd;      /* CMD id of the last CMD_ACK               */
    uint8_t  lastNackCmd;     /* CMD id of the last CMD_NACK              */
    uint8_t  lastNackReason;  /* NACK_* reason of the last CMD_NACK       */
};

/* Configure the two UARTs (pins + 1 Mbps) and reset the parsers/state. */
void channel_link_init();

/* Drain both UART RX buffers, decode frames and update link-timeout flags.
 * Call every loop iteration. */
void channel_link_task();

/* --- Brain -> Channel commands (fire-and-forget, ACK tracked in status) --- */
void channel_set_voltage(uint8_t ch, int32_t mV);
void channel_set_current(uint8_t ch, int32_t mA);
void channel_set_output (uint8_t ch, bool on);
/* Set a measurement averaging window (which = AVG_V / AVG_I, count 1..32).
 * Updates the cached ChannelStatus optimistically so the UI reflects it at once;
 * the channel confirms with a CMD_SETTINGS reply. */
void channel_set_avg    (uint8_t ch, uint8_t which, uint8_t count);
/* Set the over-temperature trip point (deg C, clamped to OTP_MIN_C..OTP_MAX_C).
 * Updates the cached ChannelStatus optimistically; the channel confirms with a
 * CMD_SETTINGS reply. */
void channel_set_otp    (uint8_t ch, uint8_t trip_c);
void channel_ping       (uint8_t ch);
void channel_get_status (uint8_t ch);
void channel_get_settings(uint8_t ch);
void channel_reset_fault(uint8_t ch);
void channel_cal_point  (uint8_t ch, uint8_t target, uint8_t index, int32_t actual);
void channel_cal_commit (uint8_t ch, uint8_t target);
void channel_cal_reset  (uint8_t ch, uint8_t target);

/* Clear the recorded last-ACK command id so a caller can send a frame and then
 * poll channel_status(ch).lastAckCmd to verify THAT frame was acknowledged
 * (frames are processed in order, so after a clear the next matching ACK
 * belongs to the frame just sent). */
void channel_clear_last_ack(uint8_t ch);

/* Read-only access to the latest snapshot for channel `ch` (0/1). */
const ChannelStatus &channel_status(uint8_t ch);

#endif /* BRAIN_CHANNEL_LINK_H */
